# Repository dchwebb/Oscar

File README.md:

# Oscar

Overview
--------

Oscar is a three channel oscilloscope, tuner, spectrum analyser and MIDI event viewer designed for use in a Eurorack modular synthesiser.

- [Manual](Oscar_Manual.md)

Version 3 changes: 
- Optimised for DIY building
    - [Build Guide](Oscar_Build_Guide.md)
    - [Bill of Materials](BOM.md)
- Illuminated buttons for quick channel selection
- USB input for firmware updates and USB MIDI analysis
- An opto-coupler and passive mult on the serial MIDI input
- Dedicated Menu button

Functional Overview
-------------------

See [Manual](Oscar_Manual.md) for more details.

- The oscilloscope can display up to three channels at once, either in separate lanes or overlaid. Horizontal and vertical zoom are available and a trigger with adjustable x/y can be applied to any channel.

- The tuner function allows for fast and accurate tuning of audio rate signals.

- The spectrum analyser is used to show the frequency components of any signal. The frequencies of the principal harmonics are shown both graphically and numerically. An autotune function dynamically adjusts the sample rate to lock on the fundamental frequency of the signal. This gives an extremely clear view of the frequency spectrum whilst being fast enough for real-time use.

- The waterfall plot shows the frequency spectrum over time in a 3 dimensional view.

- The MIDI event viewer displays the MIDI channel, note on/off status, pitchbends, control changes and aftertouch. Clock speed is indicated with a flashing dot. 

Technical
---------

Oscar uses an SMT32F446 microcontroller to capture incoming signals with the internal ADC and display the results on a 320x240 LCD display via SPI. Code is written in C++ 20 using the STM32CubeIDE Eclipse-based IDE. Hardware interfacing is carried out through custom code (ie no STM HAL libraries).

- [Schematics](Hardware_v3/Oscar_Components.pdf)

The microcontroller is clocked at 180MHz via an external 8MHz crystal oscillator. The analog inputs are scaled with an MCP6004 op-amp and the mult outputs buffered with a TL074 op-amp. The internal UART is used to capture serial MIDI data for display via a H11L1 optocoupler (to reduce the risk of ground hum).

The display is a 320x240 TFT LCD controlled with an ILI9341 driver. Screen refreshes are sent using SPI via DMA from the microcontroller. A USB C socket functions in USB 2.0 mode with an RCLAMP0502B providing ESD protection.

Analog signal capture is carried out via the internal 12 bit ADCs. Capture is controlled by a timer that is adjusted to the desired horizontal display frequency in oscilloscope mode. In Spectrum Analyser mode the autotune function dynamically alters the sampling rate to attempt to capture an integer multiple of the fundamental frequency of the incoming signal. This is done by inspecting the side-lobes of the FFT and altering the sampling rate to minimise the offset.

The tuner mode uses an overlapping FFT technique to increase accuracy. Using this mechanism samples 1 to 1024 are placed in one buffer and samples 512 to 1536 are placed in a second buffer. FFTs are carried out on each buffer and then the phase offset between the fundamental is measured. This can then be used to calculate the pitch with much enhanced accuracy for the additional processing time.

### Power Supply

The Eurorack +/-12V rails have reverse polarity protection and filtering. The 3.3V MCU and DAC digital power supplies are provided by an LT1117-3.3 linear regulator. A common digital/analog ground plane is used.

- +12V Current Draw: 151mA
- -12V Current Draw: 6mA

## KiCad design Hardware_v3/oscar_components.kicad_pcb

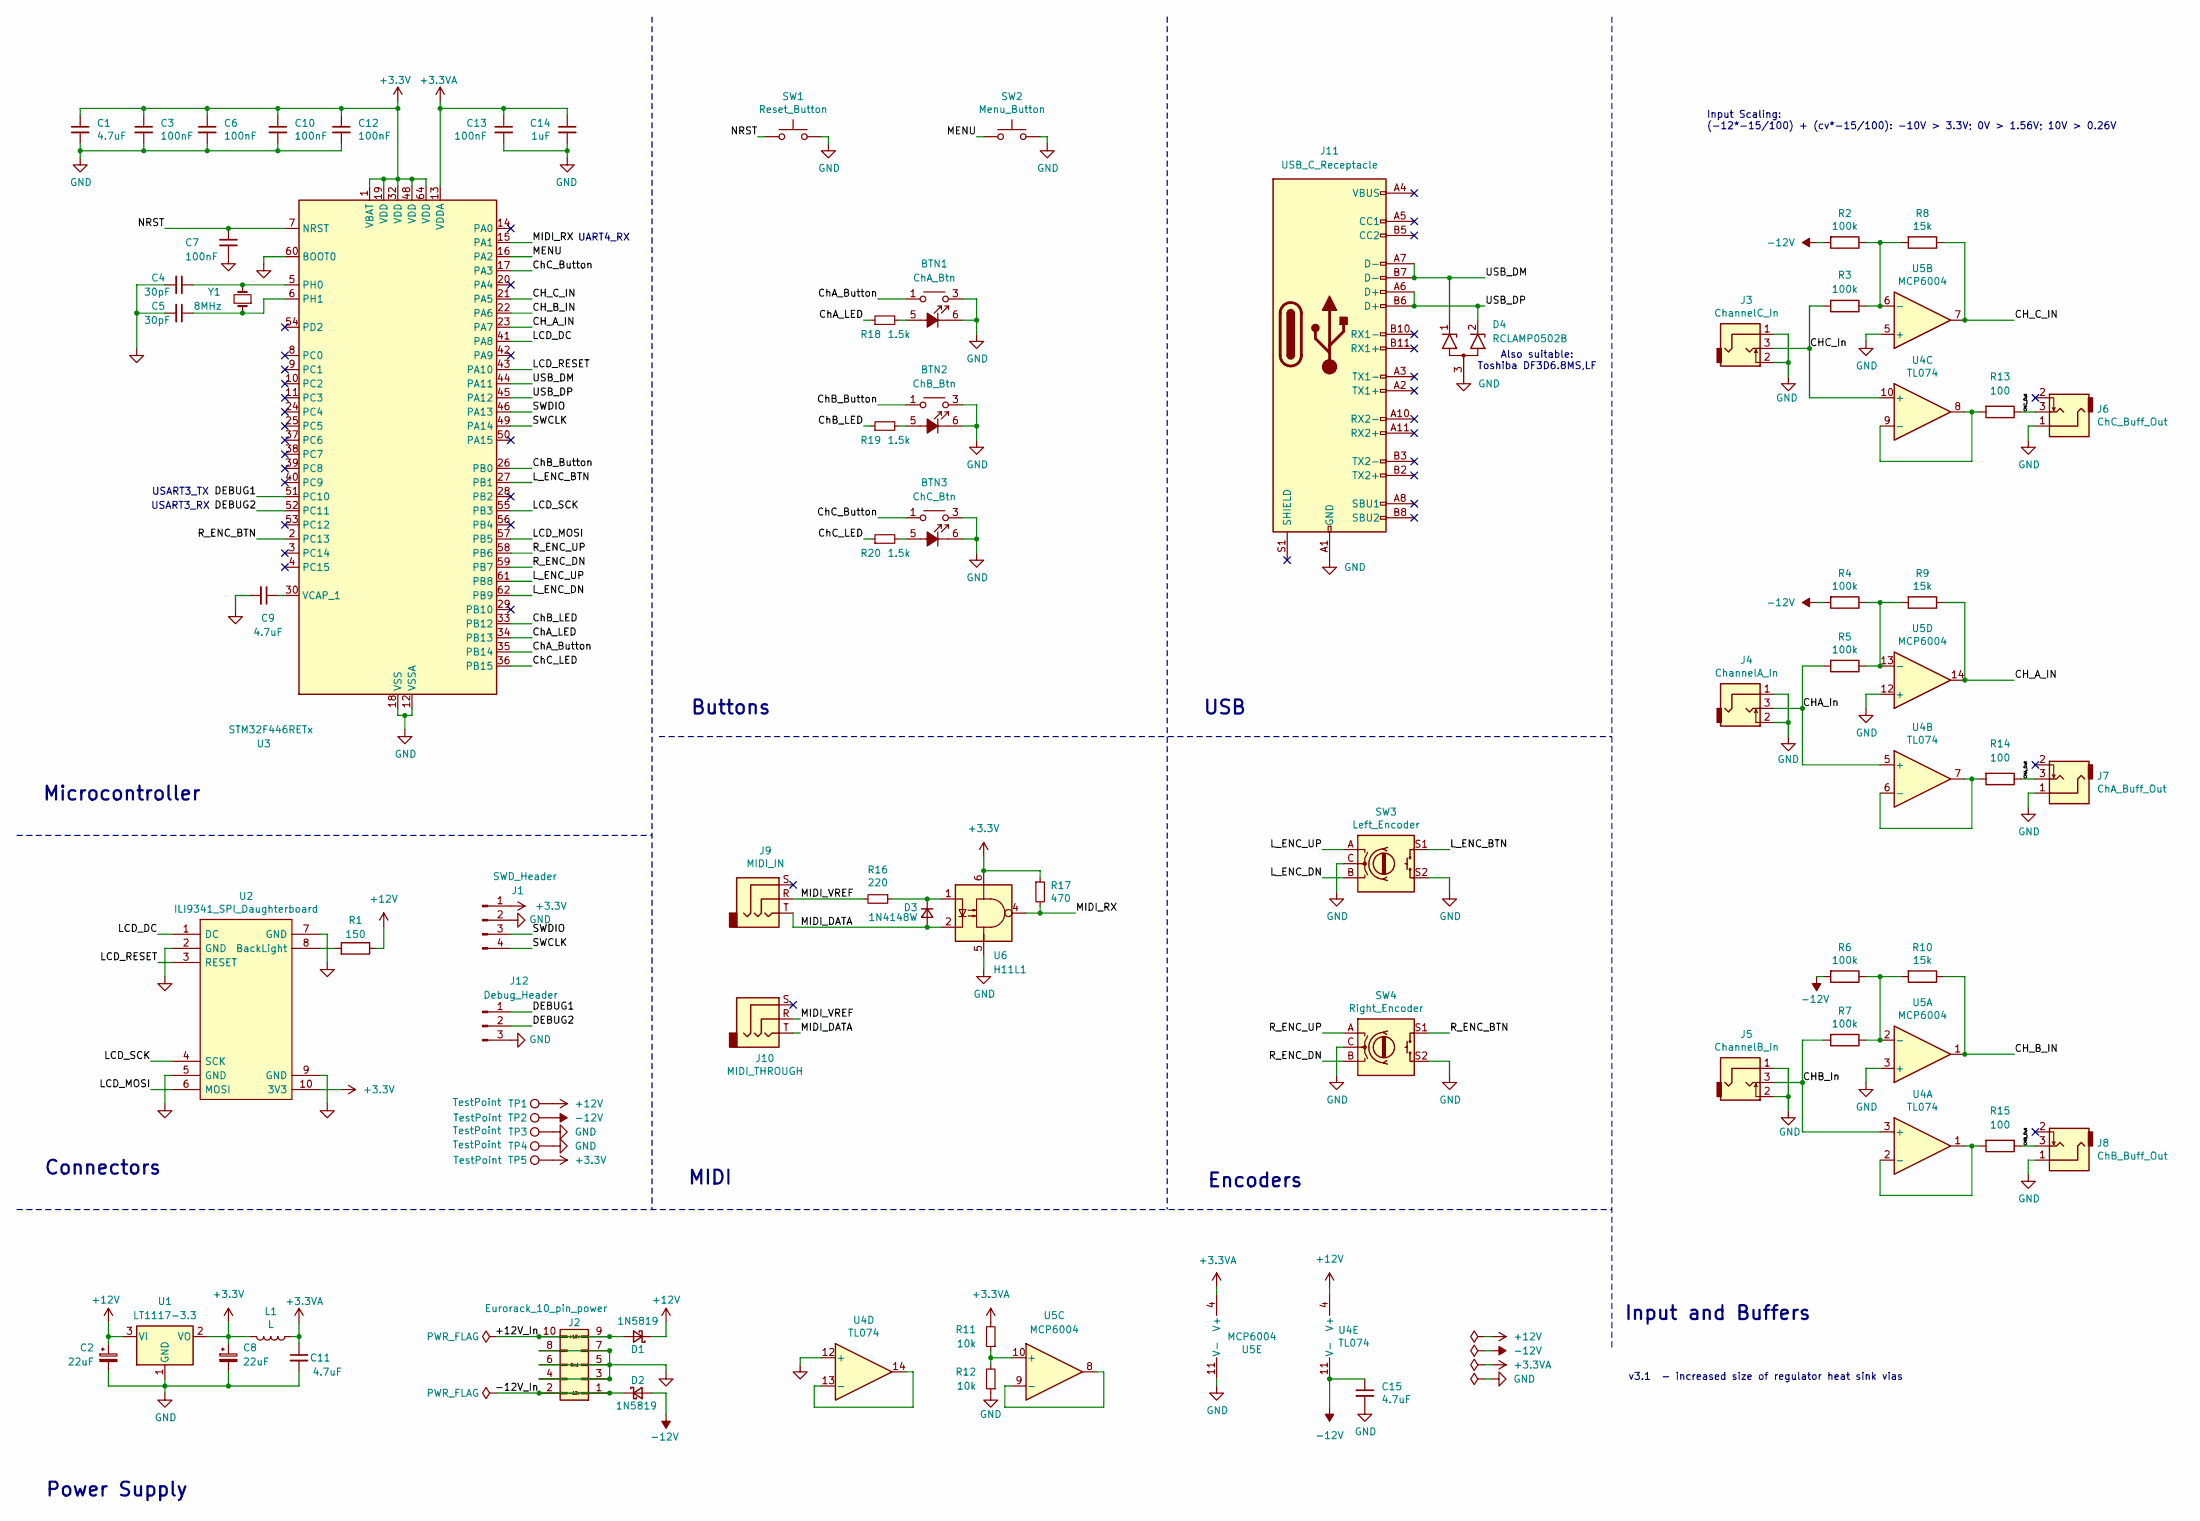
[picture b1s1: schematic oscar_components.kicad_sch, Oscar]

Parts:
BTN1: ChA_Btn; Low_Profile_LED_Button
BTN2: ChB_Btn; Low_Profile_LED_Button
BTN3: ChC_Btn; Low_Profile_LED_Button
C1, C9, C11, C15: 4.7uF; C_0805_2012Metric
C2, C8: 22uF; CP_Elec_4x5.8
C3, C6, C7, C10, C12, C13: 100nF; C_0805_2012Metric
C4, C5: 30pF; C_0603_1608Metric_Pad1.08x0.95mm_HandSolder
C14: 1uF; C_0805_2012Metric
D1, D2: 1N5819; D_SOD-123
D3: 1N4148W; D_SOD-123
D4: RCLAMP0502B; SOT-416
J1: SWD_Header; SWD_header
J2: Eurorack_10_pin_power; Eurorack_10_pin_header
J3: ChannelC_In; THONKICONN_hole
J4: ChannelA_In; THONKICONN_hole
J5: ChannelB_In; THONKICONN_hole
J6: ChC_Buff_Out; THONKICONN_hole
J7: ChA_Buff_Out; THONKICONN_hole
J8: ChB_Buff_Out; THONKICONN_hole
J9: MIDI_IN; Thonkiconn_Stereo-PJ366ST
J10: MIDI_THROUGH; Thonkiconn_Stereo-PJ366ST
J11: USB_C_Receptacle; USB_C_Receptacle_Amphenol_12401951E412A
J12: Debug_Header; PinHeader_1x03_P2.54mm_Vertical
L1: L; R_0805_2012Metric
R1: 150; R_0805_2012Metric
R2, R3, R4, R5, R6, R7: 100k; R_0805_2012Metric
R8, R9, R10: 15k; R_0805_2012Metric
R11, R12: 10k; R_0805_2012Metric; Part_Number C23162
R13, R14, R15: 100; R_0805_2012Metric
R16: 220; R_0805_2012Metric
R17: 470; R_0805_2012Metric
R18, R19, R20: 1.5k; R_0805_2012Metric; Part_Number C23162
SW1: Reset_Button; SW_PUSH_6mm_aligned
SW2: Menu_Button; SW_PUSH_6mm_aligned
SW3: Left_Encoder; Encoder
SW4: Right_Encoder; Encoder
TP1, TP2, TP3, TP4, TP5: TestPoint; 1.3mm_Test_Point
U1: LT1117-3.3; SOT-223-3_TabPin2
U2: ILI9341_SPI_Daughterboard; ILI9341_SPI_daughterboard_v2
U3: STM32F446RETx; LQFP-64_10x10mm_P0.5mm
U4: TL074; SOIC-14_3.9x8.7mm_P1.27mm
U5: MCP6004; SOIC-14_3.9x8.7mm_P1.27mm
U6: H11L1
Y1: 8MHz; Crystal_SMD_5032-2Pin_5.0x3.2mm_Large_Pads

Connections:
+3.3V: C1.1, C3.1, C6.1, C8.1, C10.1, C12.1, J1.1, L1.2, R17.1, TP5.1, U1.2 (VO), U2.10 (3V3), U3.1 (VBAT), U3.19 (VDD), U3.32 (VDD), U3.48 (VDD), U3.64 (VDD), U6.6
+3.3VA: C11.1, C13.1, C14.1, L1.1, R11.2, U3.13 (VDDA), U5.4 (V+)
+12V: C2.1, D1.1 (K), R1.1, TP1.1, U1.3 (VI), U4.4 (V+)
-12V: C15.1, D2.2 (A), R2.2, R4.2, R6.2, TP2.1, U4.11 (V-)
/+12V_In: D1.2 (A), J2.9, J2.10
/-12V_In: D2.1 (K), J2.1, J2.2
/CHA_In: J4.3, R5.2, U4.5 (+)
/CHA_Out: J7.3, R14.1
/CHB_In: J5.3, R7.2, U4.3 (+)
/CHB_Out: J8.3, R15.1
/CHC_In: J3.3, R3.2, U4.10 (+)
/CHC_Out: J6.3, R13.1
/CH_A_IN: R9.1, U3.23 (PA7), U5.14
/CH_B_IN: R10.1, U3.22 (PA6), U5.1
/CH_C_IN: R8.1, U3.21 (PA5), U5.7
/ChA_Button: BTN1.1, BTN1.2, U3.35 (PB14)
/ChA_LED: R18.1, U3.34 (PB13)
/ChB_Button: BTN2.1, BTN2.2, U3.26 (PB0)
/ChB_LED: R19.1, U3.33 (PB12)
/ChC_Button: BTN3.1, BTN3.2, U3.17 (PA3)
/ChC_LED: R20.1, U3.36 (PB15)
/DEBUG1: J12.1, U3.51 (PC10)
/DEBUG2: J12.2, U3.52 (PC11)
/LCD_DC: U2.1 (DC), U3.41 (PA8)
/LCD_MOSI: U2.6 (MOSI), U3.57 (PB5)
/LCD_RESET: U2.3 (RESET), U3.43 (PA10)
/LCD_SCK: U2.4 (SCK), U3.55 (PB3)
/L_ENC_BTN: SW3.S1, U3.27 (PB1)
/L_ENC_DN: SW3.B, U3.62 (PB9)
/L_ENC_UP: SW3.A, U3.61 (PB8)
/MENU: SW2.1, U3.16 (PA2)
/MIDI_DATA: D3.2 (A), J9.T, J10.T, U6.2
/MIDI_RX: R17.2, U3.15 (PA1), U6.4
/MIDI_VREF: J9.R, J10.R, R16.2
/NRST: C7.1, SW1.1, U3.7 (NRST)
/R_ENC_BTN: SW4.S1, U3.2 (PC13)
/R_ENC_DN: SW4.B, U3.59 (PB7)
/R_ENC_UP: SW4.A, U3.58 (PB6)
/SWCLK: J1.4, U3.49 (PA14)
/SWDIO: J1.3, U3.46 (PA13)
/USB_DM: D4.1 (K1), J11.A7 (D-), J11.B7 (D-), U3.44 (PA11)
/USB_DP: D4.2 (K2), J11.A6 (D+), J11.B6 (D+), U3.45 (PA12)
GND: BTN1.3, BTN1.4, BTN1.6 (K), BTN2.3, BTN2.4, BTN2.6 (K), BTN3.3, BTN3.4, BTN3.6 (K), C1.2, C2.2, C3.2, C4.2, C5.2, C6.2, C7.2, C8.2, C9.2, C10.2, C11.2, C12.2, C13.2, C14.2, C15.2, D4.3 (A), J1.2, J2.3, J2.4, J2.5, J2.6, J2.7, J2.8, J3.1, J3.2, J4.1, J4.2, J5.1, J5.2, J6.1, J7.1, J8.1, J11.A1 (GND), J11.A12 (GND), J11.B1 (GND), J11.B12 (GND), J12.3, R12.1, SW1.2, SW2.2, SW3.C, SW3.S2, SW4.C, SW4.S2, TP3.1, TP4.1, U1.1 (GND), U2.2 (GND), U2.5 (GND), U2.7 (GND), U2.9 (GND), U3.12 (VSSA), U3.18 (VSS), U3.31 (VSS), U3.47 (VSS), U3.60 (BOOT0), U3.63 (VSS), U4.12 (+), U5.3 (+), U5.5 (+), U5.11 (V-), U5.12 (+), U6.5
unnamed: BTN1.5 (A), R18.2
unnamed: BTN2.5 (A), R19.2
unnamed: BTN3.5 (A), R20.2
unnamed: D3.1 (K), R16.1, U6.1
unnamed: R1.2, U2.8 (BackLight)
unnamed: C4.1, U3.5 (PH0), Y1.2
unnamed: C5.1, U3.6 (PH1), Y1.1
unnamed: C9.1, U3.30 (VCAP_1)
unnamed: R15.2, U4.1, U4.2 (-)
unnamed: R14.2, U4.6 (-), U4.7
unnamed: R13.2, U4.8, U4.9 (-)
unnamed: U4.13 (-), U4.14
unnamed: R6.1, R7.1, R10.2, U5.2 (-)
unnamed: R2.1, R3.1, R8.2, U5.6 (-)
unnamed: R11.1, R12.2, U5.10 (+)
unnamed: U5.8, U5.9 (-)
unnamed: R4.1, R5.1, R9.2, U5.13 (-)

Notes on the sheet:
MIDI
Buttons
USART3_TX
Also suitable: Toshiba DF3D6.8MS,LF
v3.1 - increased size of regulator heat sink vias
Encoders
Microcontroller
Input Scaling: (-12*-15/100) + (cv*-15/100): -10V > 3.3V; 0V > 1.56V; 10V > 0.26V
USART3_RX
UART4_RX
Input and Buffers
Connectors
Power Supply
USB

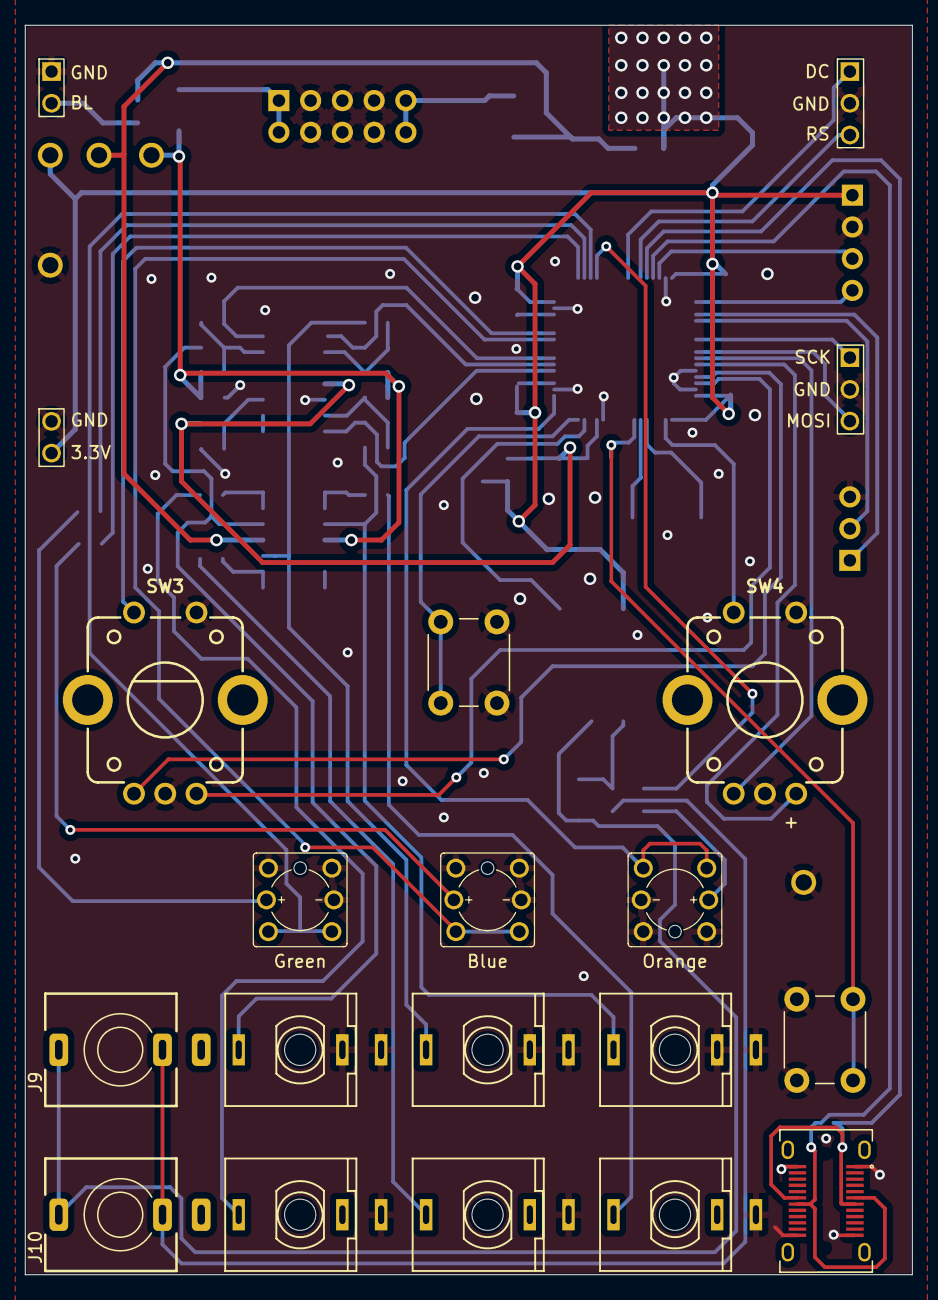
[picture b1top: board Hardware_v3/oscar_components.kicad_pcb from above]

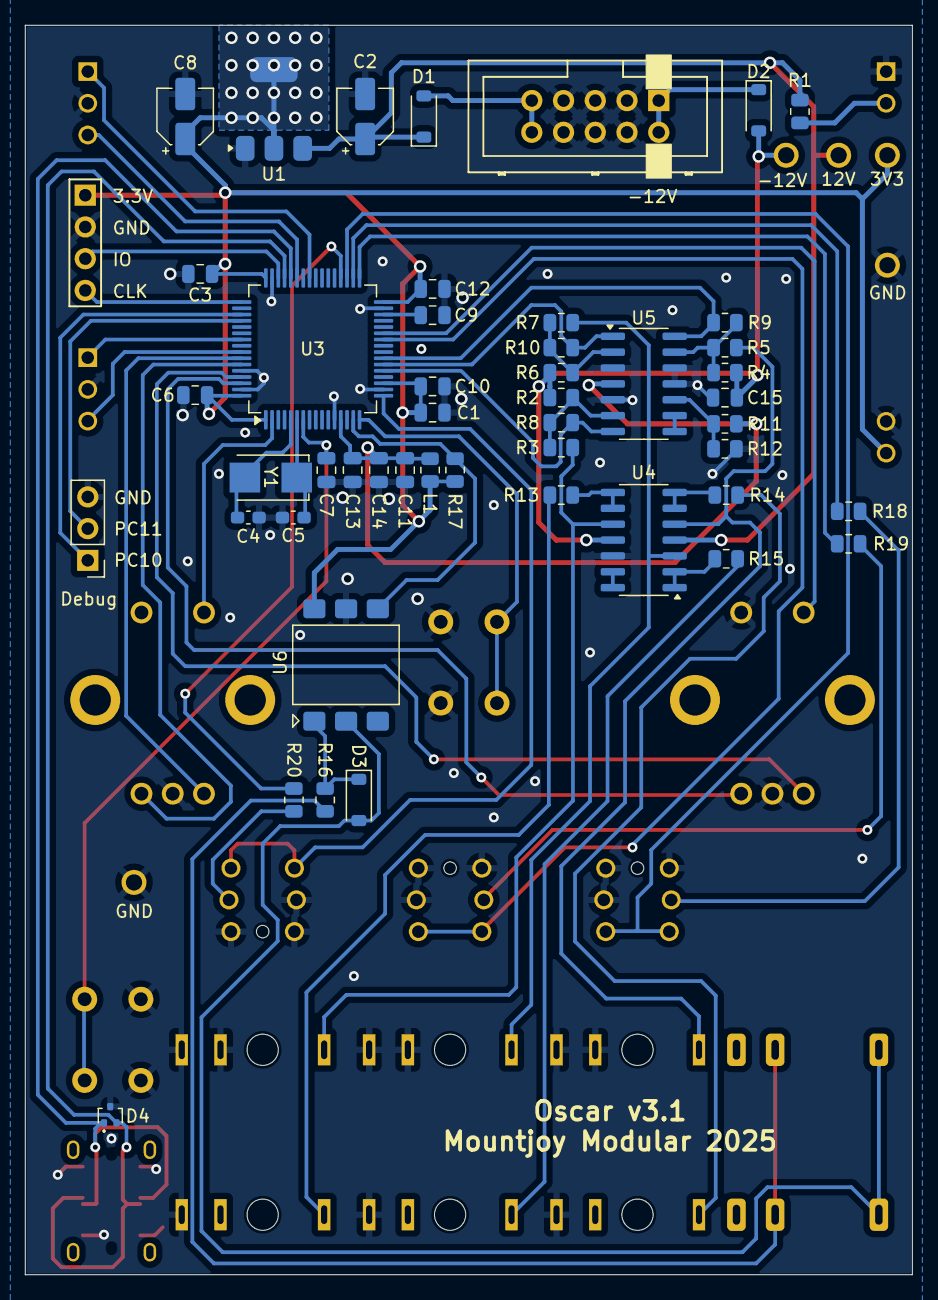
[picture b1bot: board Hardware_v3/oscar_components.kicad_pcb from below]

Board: 4 copper layers, 71.0 x 100.0 mm, 71 parts (49 on the bottom side), 60 nets.

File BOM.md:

# Oscar v3 BOM

## Screen

- [2.4 inch TFT HD Color LCD Screen 2.8-3.3V 240x320 4-wire SPI interface ILI9341](https://www.ebay.co.uk/itm/394725476377)
- Various lengths of 2.54mm pin headers

## Generic Parts (optional if using JLC assembly)

|Value        |Designator          |Footprint                                  |JLC     |
|-------------|--------------------|-------------------------------------------|--------|
|8MHz         |Y1                  |Crystal 5032 2 Pin 5.0x3.2mm               |C115962 |
|STM32F446RETx|U3                  |LQFP-64_10x10mm_P0.5mm                     |C69336  |
|H11L1        |U6                  |H11L1 Optocoupler                          |C20082  |
|RCLAMP0502B  |D4                  |SOT-416 ESD Protection for USB             |C5370962|
|LT1117-3.3   |U1                  |SOT-223-3 TabPin2 Linear Regulator         |C6186   |
|TL074        |U4                  |SOIC-14_3.9x8.7mm_P1.27mm OpAmp            |C107644 |
|MCP6004      |U5                  |SOIC-14_3.9x8.7mm_P1.27mm OpAmp            |C7378   |
|1N4148W      |D3                  |D_SOD-123 Diode                            |C81598  |
|1N5819       |D1,D2               |D_SOD-123 Diode                            |C8598   |
|Ferrite Bead |L1                  |0805 300mΩ 600Ω@100MHz Ferrite Bead        |C1017   |
|22uF 16V     |C2,C8               |Electrolytic Capacitor 4 x 5.8mm           |C134793 |
|4.7uF        |C1,C11,C15,C9       |0805 Capacitor                             |C1779   |
|1uF          |C14                 |0805 Capacitor                             |C28323  |
|100nF        |C10,C12,C13,C3,C6,C7|0805 Capacitor                             |C49678  |
|30pF         |C4,C5               |0603 Capacitor                             |C1658   |
|100          |R13,R14,R15         |0805 1% Resistor                           |C17408  |
|150          |R1                  |0805 1% Resistor                           |C17471  |
|220          |R16                 |0805 1% Resistor                           |C17557  |
|470          |R17                 |0805 1% Resistor                           |C17710  |
|1.5k         |R18,R19,R20         |0805 1% Resistor                           |C4310   |
|10k          |R11,R12             |0805 1% Resistor                           |C17414  |
|15k          |R10,R8,R9           |0805 1% Resistor                           |C17475  |
|100k         |R2,R3,R4,R5,R6,R7   |0805 1% Resistor                           |C149504 |

## Digikey/Mouser Components

|Comment      |Designator          |Footprint                                   |Digikey               |Mouser              |
|-------------|--------------------|--------------------------------------------|----------------------|--------------------|
|Menu Button  |SW2                 |Tactile Switch SKHHDTA010                   |4809-SKHHDTA010-ND    |688-SKHHDT          |
|Reset Button |SW1                 |Tactile Switch SKHHDTA010                   |4809-SKHHDTA010-ND    |688-SKHHDT          |
|Right Encoder|SW4                 |Rotary Encoder PEC11R-4220F-S0024           |PEC11R-4220F-S0024-ND |652-PEC11R-4220F-S24|
|Left Encoder |SW3                 |Rotary Encoder PEC11R-4220F-S0024           |PEC11R-4220F-S0024-ND |652-PEC11R-4220F-S24|
|USB C Socket |J11                 |Amphenol 12401951E412A                      |664-12401951E412ATR-ND|523-12401951E412A   |
|Eurorack 10 pin power|J2          |Eurorack 10 pin shrouded header             |SAM10831-ND           |200-TST10501TD      |


## Thonk Components

|Comment      |Designator          |Footprint                                  |Thonk   |
|-------------|--------------------|-------------------------------------------|--------|
|ChA Btn      |BTN1                |Low Profile LED Button                     |[Low-Profile LED Button - GREEN](https://www.thonk.co.uk/shop/low-profile-led-buttons/)|
|ChB Btn      |BTN2                |Low Profile LED Button                     |[Low-Profile LED Button - BLUE](https://www.thonk.co.uk/shop/low-profile-led-buttons/)|
|ChC Btn      |BTN3                |Low Profile LED Button                     |[Low-Profile LED Button - ORANGE](https://www.thonk.co.uk/shop/low-profile-led-buttons/)|
|ChannelA In  |J4                  |THONKICONN hole                            |[Thonkiconn Mono 3.5mm Audio Jacks (WQP518MA)](https://www.thonk.co.uk/shop/thonkiconn/)|
|ChannelB In  |J5                  |THONKICONN hole                            |[Thonkiconn Mono 3.5mm Audio Jacks (WQP518MA)](https://www.thonk.co.uk/shop/thonkiconn/)|
|ChA Buff Out |J7                  |THONKICONN hole                            |[Thonkiconn Mono 3.5mm Audio Jacks (WQP518MA)](https://www.thonk.co.uk/shop/thonkiconn/)|
|ChB Buff Out |J8                  |THONKICONN hole                            |[Thonkiconn Mono 3.5mm Audio Jacks (WQP518MA)](https://www.thonk.co.uk/shop/thonkiconn/)|
|ChC Buff Out |J6                  |THONKICONN hole                            |[Thonkiconn Mono 3.5mm Audio Jacks (WQP518MA)](https://www.thonk.co.uk/shop/thonkiconn/)|
|ChannelC In  |J3                  |THONKICONN hole                            |[Thonkiconn Mono 3.5mm Audio Jacks (WQP518MA)](https://www.thonk.co.uk/shop/thonkiconn/)|
|MIDI IN      |J9                  |Thonkiconn Stereo-PJ366ST                  |[Green Thonkiconn Stereo 3.5mm Audio Jacks (PJ366ST)](https://www.thonk.co.uk/shop/thonkiconn/)|
|MIDI THROUGH |J10                 |Thonkiconn Stereo-PJ366ST                  |[Green Thonkiconn Stereo 3.5mm Audio Jacks (PJ366ST)](https://www.thonk.co.uk/shop/thonkiconn/)|

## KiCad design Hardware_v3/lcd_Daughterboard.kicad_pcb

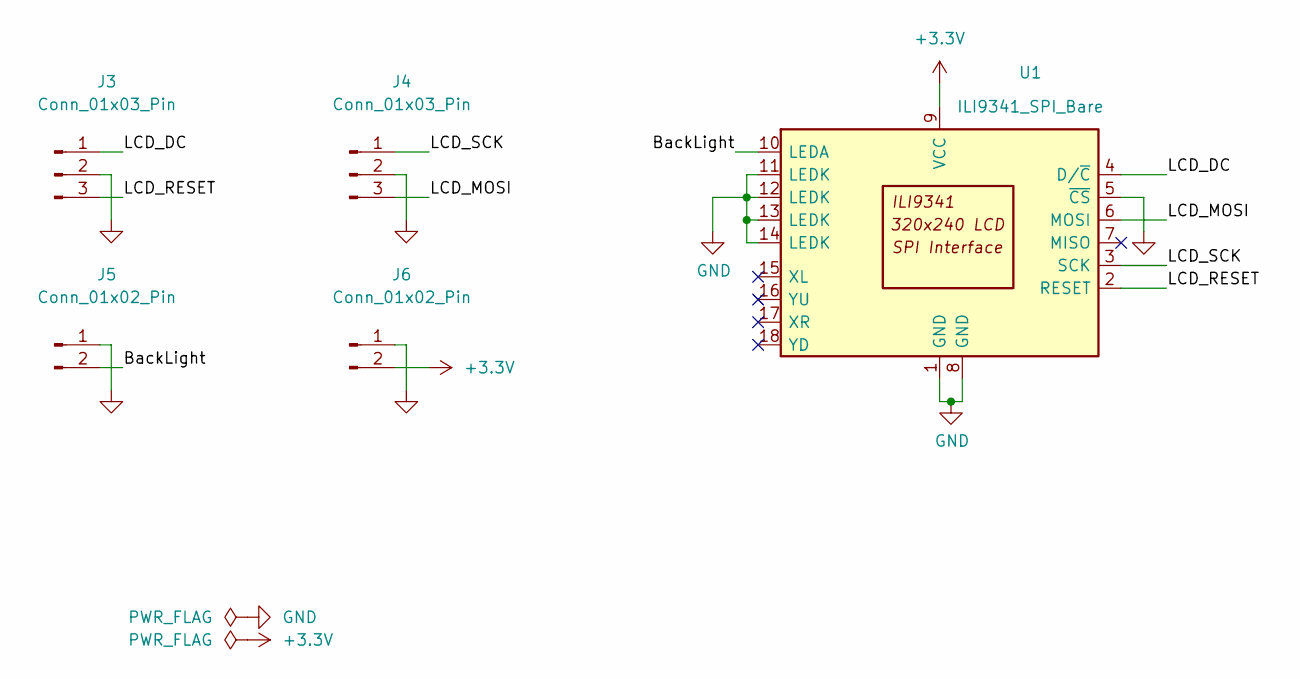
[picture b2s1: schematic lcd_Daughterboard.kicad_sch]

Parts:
J3, J4: Conn_01x03_Pin; PinHeader_1x03_P2.54mm_Vertical
J5, J6: Conn_01x02_Pin; PinHeader_1x02_P2.54mm_Vertical
U1: ILI9341_SPI_Bare; 18x0.8mmLCDConnector

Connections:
+3.3V: J6.2, U1.9 (VCC)
/BackLight: J5.2, U1.10 (LEDA)
/LCD_DC: J3.1, U1.4 (D/~C)
/LCD_MOSI: J4.3, U1.6 (MOSI)
/LCD_RESET: J3.3, U1.2 (RESET)
/LCD_SCK: J4.1, U1.3 (SCK)
GND: J3.2, J4.2, J5.1, J6.1, U1.1 (GND), U1.5 (~CS), U1.8 (GND), U1.11 (LEDK), U1.12 (LEDK), U1.13 (LEDK), U1.14 (LEDK)

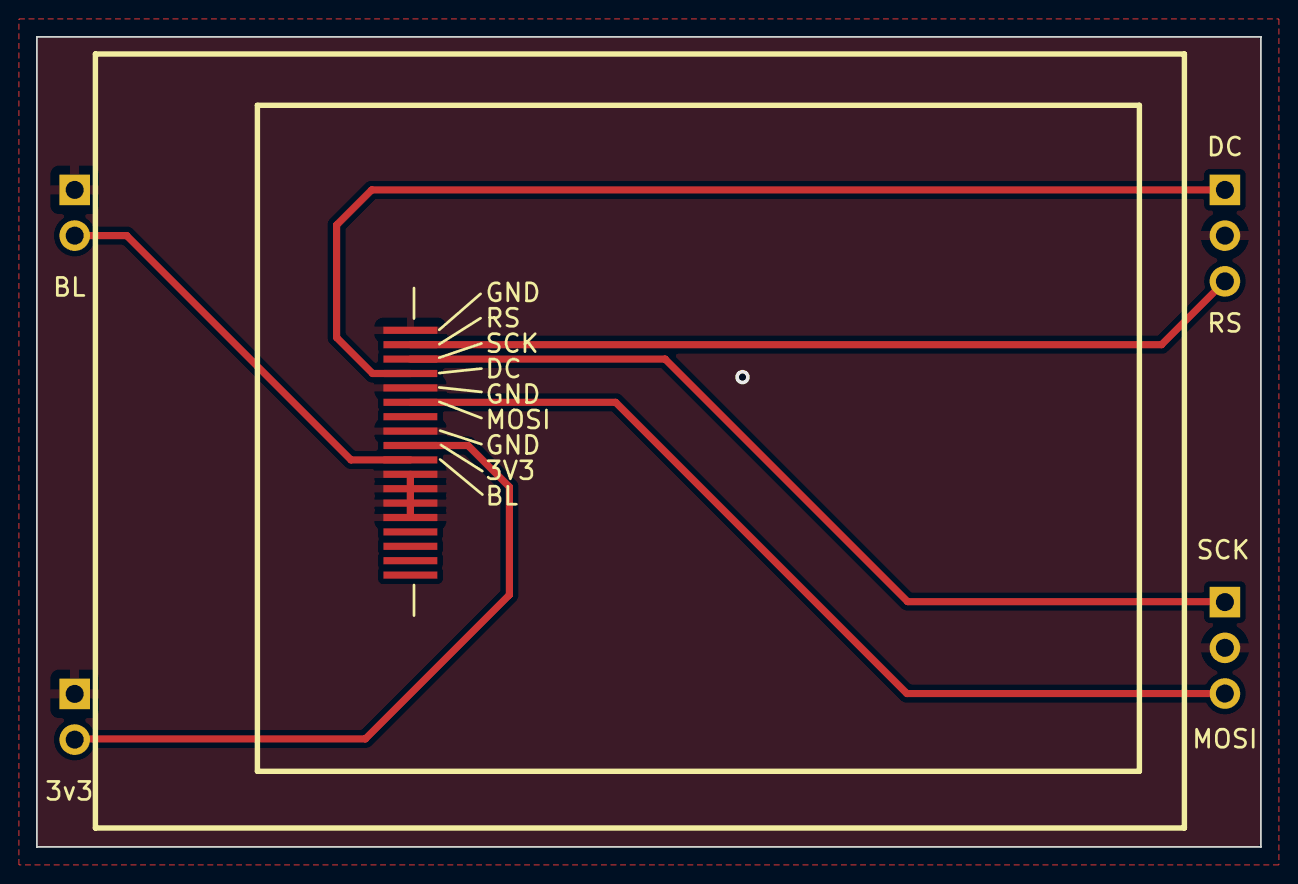
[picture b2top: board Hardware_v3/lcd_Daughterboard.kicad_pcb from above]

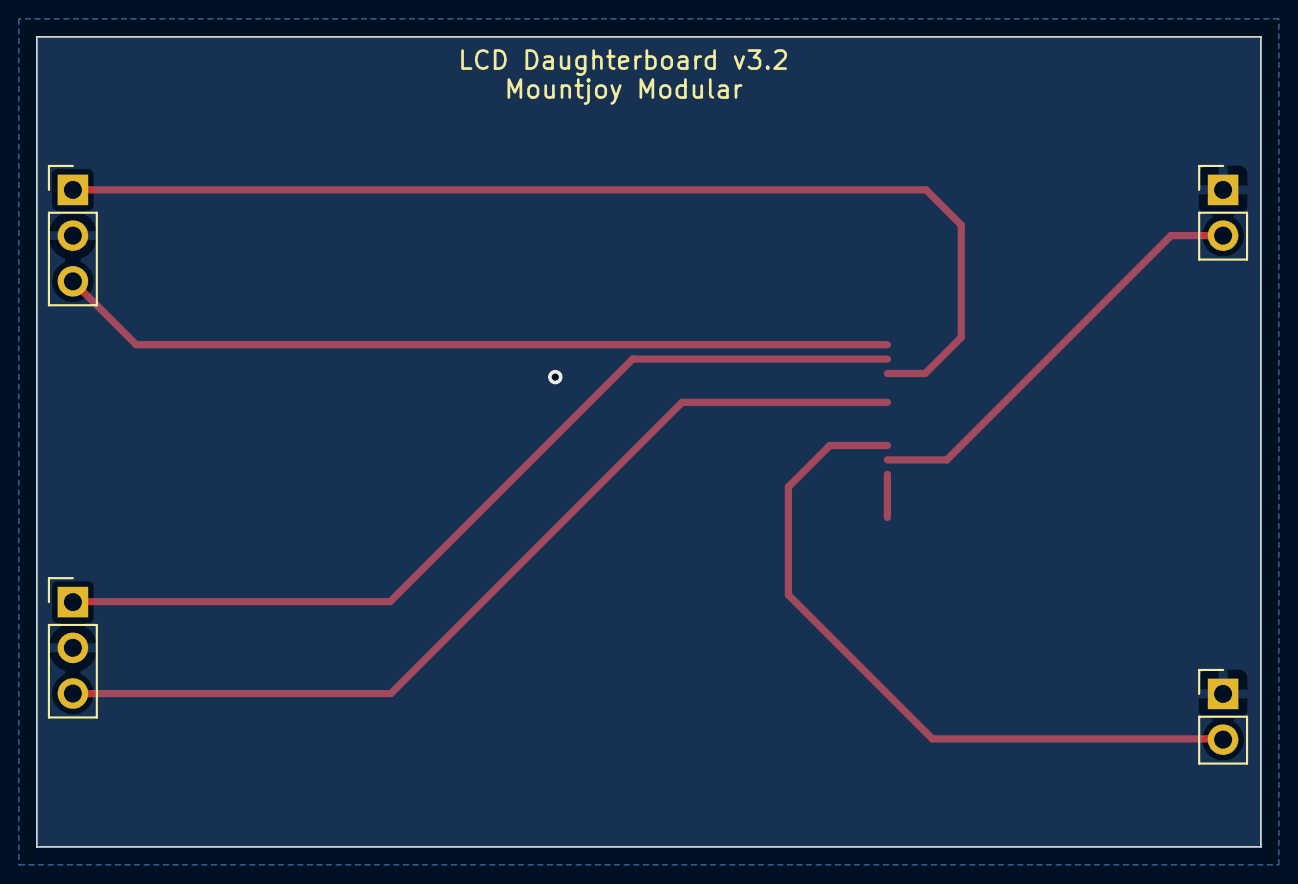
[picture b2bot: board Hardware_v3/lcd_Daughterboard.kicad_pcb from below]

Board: 2 copper layers, 68.0 x 45.0 mm, 5 parts (4 on the bottom side), 7 nets.

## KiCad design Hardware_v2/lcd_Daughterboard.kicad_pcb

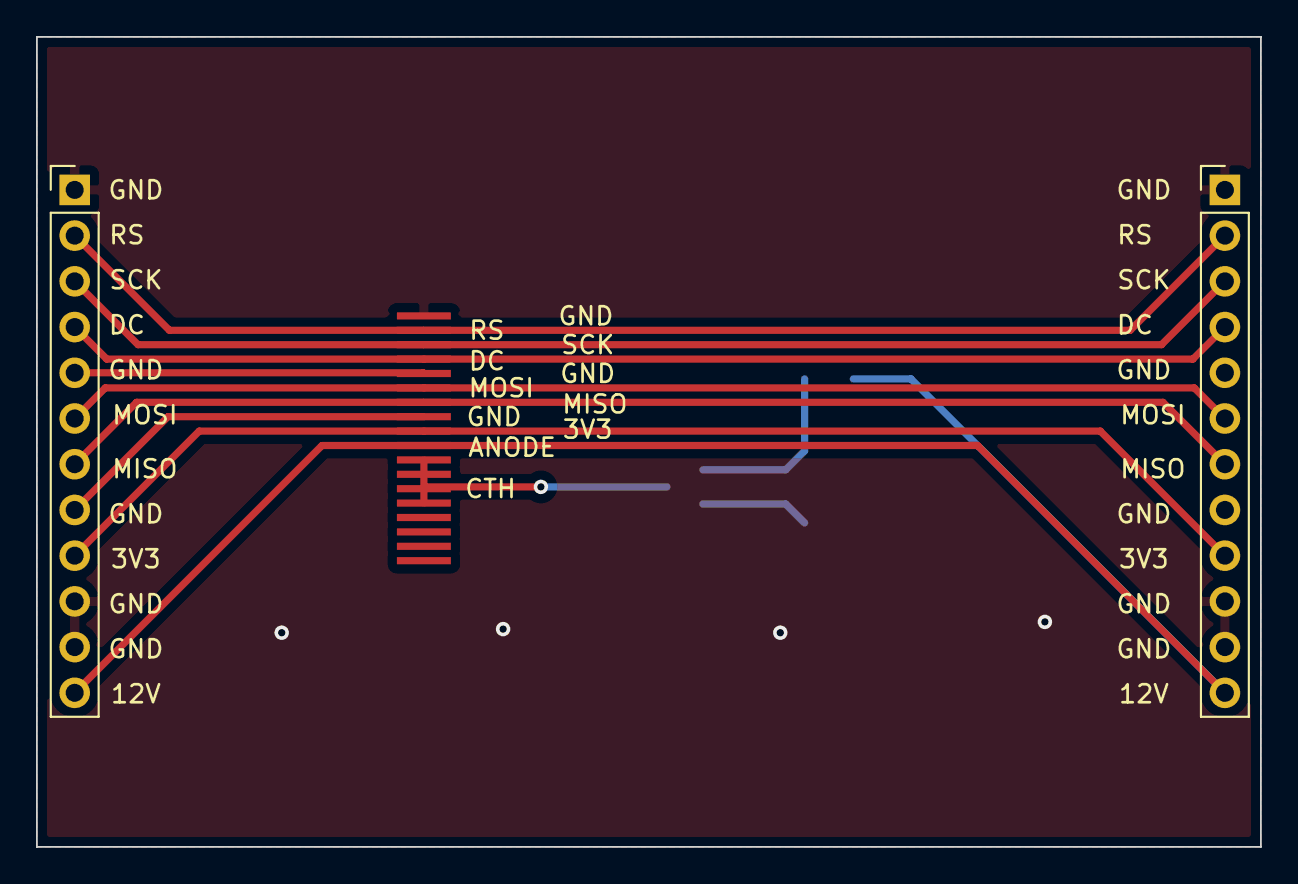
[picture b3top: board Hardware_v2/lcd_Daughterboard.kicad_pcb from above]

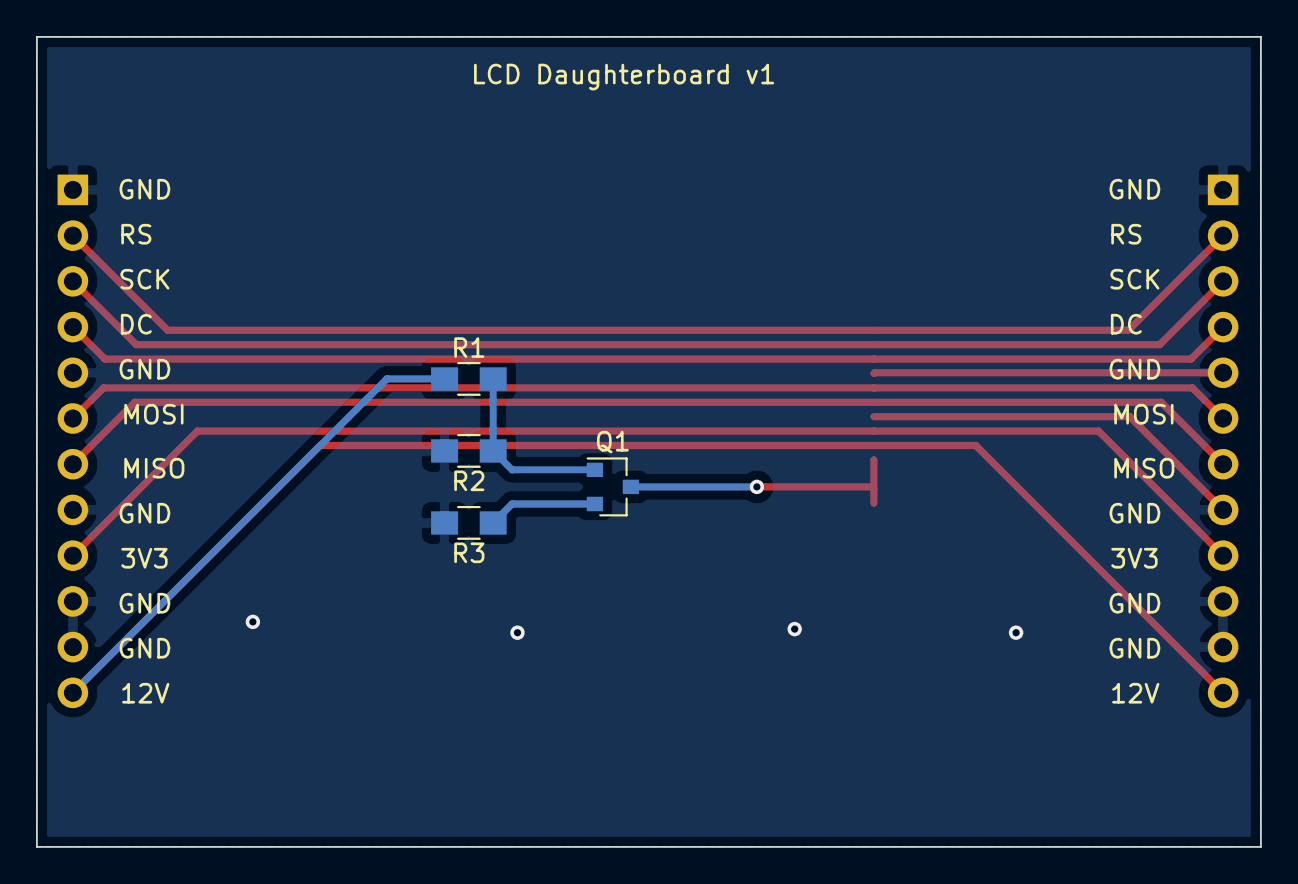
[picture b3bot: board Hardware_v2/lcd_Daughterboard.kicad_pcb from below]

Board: 2 copper layers, 68.0 x 45.0 mm, 7 parts (4 on the bottom side), 11 nets.

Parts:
J1, J2: Conn_01x12; Pin_Header_Straight_1x12_Pitch2.54mm
Q1: MMBT3904; SOT-23
R1: 220; R_0805_HandSoldering
R2: 1k; R_0805_HandSoldering
R3: 100; R_0805_HandSoldering
U1: ILI9341_SPI_Bare; 18x0.8mmLCDConnector

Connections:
+3V3: J1.9, J2.9, U1.9
GND: J1.1, J1.5, J1.8, J1.10, J1.11, J2.1, J2.5, J2.8, J2.10, J2.11, R2.2, R3.2, U1.1, U1.5, U1.8
LCD_CATHODE: Q1.3, U1.11, U1.12, U1.13, U1.14
LCD_DC: J1.4, J2.4, U1.4
LCD_MISO: J1.7, J2.7, U1.7
LCD_MOSI: J1.6, J2.6, U1.6
LCD_RESET: J1.2, J2.2, U1.2
LCD_SCK: J1.3, J2.3, U1.3
unnamed: Q1.1, R1.2, R2.1
unnamed: Q1.2, R3.1
VCC: J1.12, J2.12, R1.1, U1.10
